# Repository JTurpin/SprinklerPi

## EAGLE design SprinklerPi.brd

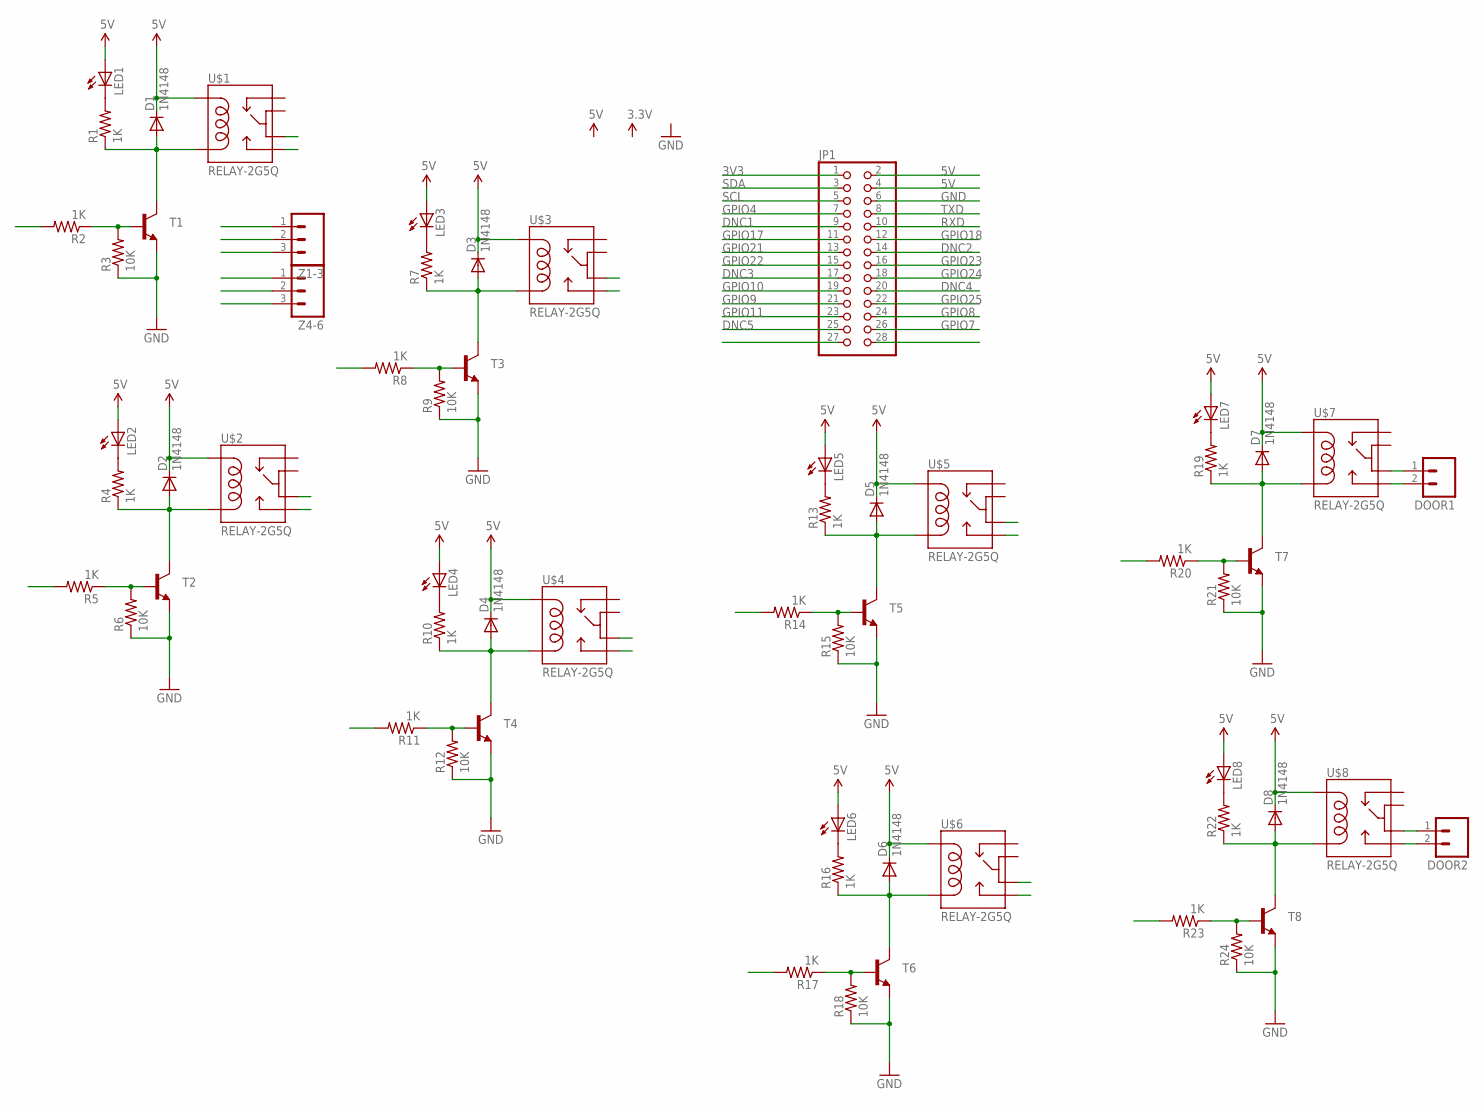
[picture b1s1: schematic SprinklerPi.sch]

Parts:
D1, D2, D3, D4, D5, D6, D7, D8: 1N4148; DIODE-1N4148
DOOR1, DOOR2: M023.5MM; SCREWTERMINAL-3.5MM-2
JP1: PINHD-2X14-CB; 2X14-CLEANBIG
LED1, LED2, LED3, LED4, LED5, LED6, LED7, LED8: LED-RED1206; LED-1206
R1, R2, R4, R5, R7, R8, R10, R11, R13, R14, R16, R17, R19, R20, R22, R23: 1K; 0805
R3, R6, R9, R12, R15, R18, R21, R24: 10K; 0805
T1, T2, T3, T4, T5, T6, T7, T8: TRANSISTOR_NPNSOT23; SOT23
U$1, U$2, U$3, U$4, U$5, U$6, U$7, U$8: RELAY-2G5Q; RELAY-G5V
Z1-3, Z4-6: M03SCREW; SCREWTERMINAL-3.5MM-3

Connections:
3V3: JP1.1
5V: D1.C, D2.C, D3.C, D4.C, D5.C, D6.C, D7.C, D8.C, JP1.2, JP1.4, LED1.A, LED2.A, LED3.A, LED4.A, LED5.A, LED6.A, LED7.A, LED8.A, U$1.2, U$2.2, U$3.2, U$4.2, U$5.2, U$6.2, U$7.2, U$8.2
DNC1: JP1.9
DNC2: JP1.14
DNC3: JP1.17
DNC4: JP1.20
DNC5: JP1.25
GND: JP1.6, R3.1, R6.1, R9.1, R12.1, R15.1, R18.1, R21.1, R24.1, T1.2 (E), T2.2 (E), T3.2 (E), T4.2 (E), T5.2 (E), T6.2 (E), T7.2 (E), T8.2 (E)
GPIO4: JP1.7
GPIO7: JP1.26
GPIO8: JP1.24
GPIO9: JP1.21
GPIO10: JP1.19
GPIO11: JP1.23
GPIO17: JP1.11
GPIO18: JP1.12
GPIO21: JP1.13
GPIO22: JP1.15
GPIO23: JP1.16
GPIO24: JP1.18
GPIO25: JP1.22
unnamed: D1.A, R1.1, T1.3 (C), U$1.9
unnamed: LED1.C, R1.2
unnamed: D7.A, R19.1, T7.3 (C), U$7.9
unnamed: R2.1, R3.2, T1.1 (B)
unnamed: D2.A, R4.1, T2.3 (C), U$2.9
unnamed: LED2.C, R4.2
unnamed: R5.1, R6.2, T2.1 (B)
unnamed: D3.A, R7.1, T3.3 (C), U$3.9
unnamed: LED3.C, R7.2
unnamed: R8.1, R9.2, T3.1 (B)
unnamed: D4.A, R10.1, T4.3 (C), U$4.9
unnamed: LED4.C, R10.2
unnamed: R11.1, R12.2, T4.1 (B)
unnamed: D5.A, R13.1, T5.3 (C), U$5.9
unnamed: LED5.C, R13.2
unnamed: R14.1, R15.2, T5.1 (B)
unnamed: D6.A, R16.1, T6.3 (C), U$6.9
unnamed: LED6.C, R16.2
unnamed: R17.1, R18.2, T6.1 (B)
unnamed: LED7.C, R19.2
unnamed: R20.1, R21.2, T7.1 (B)
unnamed: DOOR1.1, U$7.6
unnamed: D8.A, R22.1, T8.3 (C), U$8.9
unnamed: LED8.C, R22.2
unnamed: R23.1, R24.2, T8.1 (B)
unnamed: DOOR2.1, U$8.6
unnamed: DOOR2.2, U$8.10
RXD: JP1.10
SCL: JP1.5
SDA: JP1.3
TXD: JP1.8
Z1: U$1.10, Z1-3.1
Z2: U$2.10, Z1-3.2
Z3: U$3.10, Z1-3.3
Z4: U$4.10, Z4-6.1
Z5: U$5.10, Z4-6.2
Z6: U$6.10, Z4-6.3
Z7: DOOR1.2, U$7.10

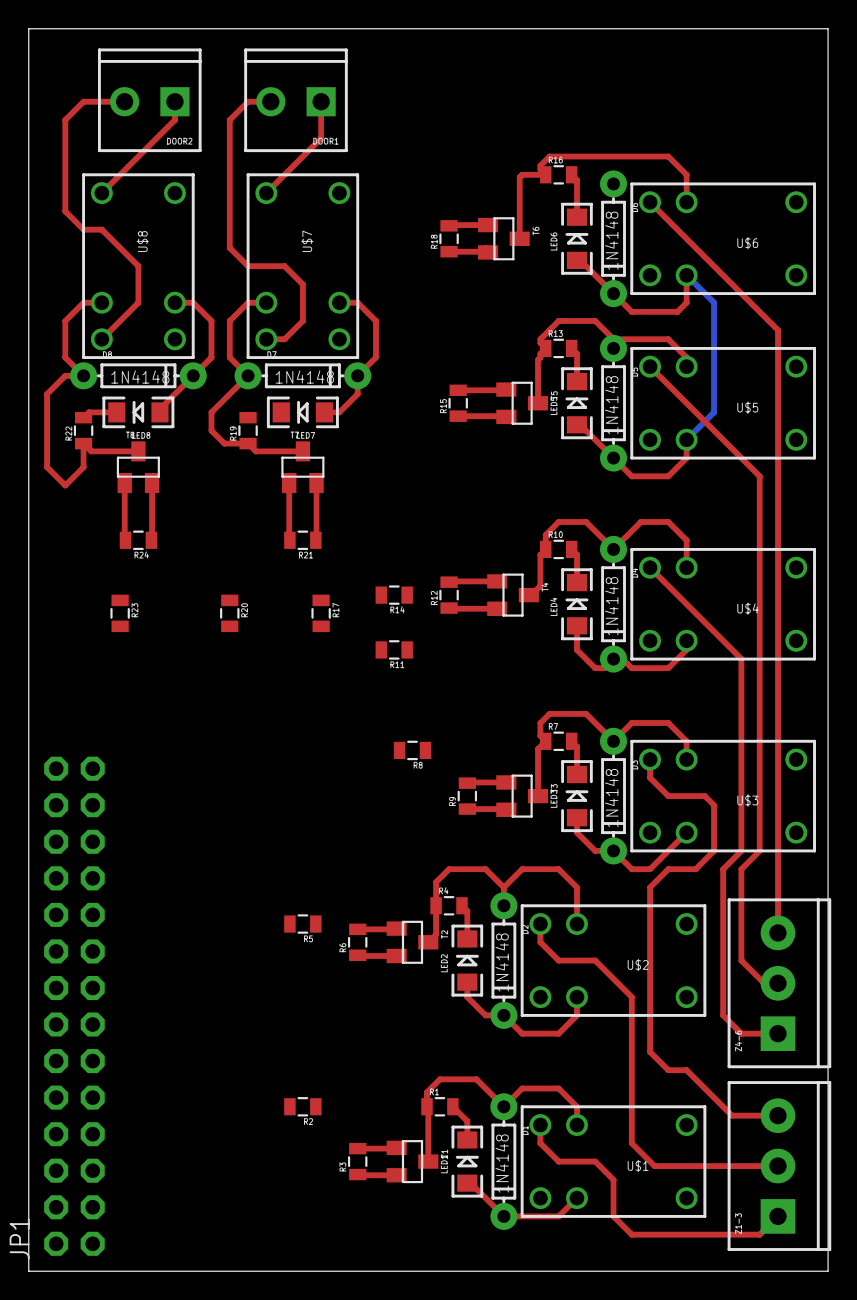
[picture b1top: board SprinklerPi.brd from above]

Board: 2 copper layers, 55.5 x 86.3 mm, 61 parts (0 on the bottom side), 36 nets.

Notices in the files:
parts and their libraries:
SparkFun-Electromechanical: Licensing: CC v3.0 Share-Alike You are welcome to use this library for commercial purposes.
